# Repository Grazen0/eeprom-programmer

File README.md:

# EEPROM Programmer

Code to program an AT28C256 EEPROM using an Arduino MEGA. Consists of [firmware](firmware) for an Arduino Mega 2560, and an [uploader](uploader) that talks to the firmware via serial USB.

## Hardware

The firmware is designed to work with a custom-made board that can be inserted on top of the Arduino's side pin column.

|  |  |
| :-------------------------------------------------------: | :---------------------------------------------------------------------------: |

The schematic is as follows:

The pins labeled "Arduino MEGA" go on top the rightmost header columns of the Arduino.

## Usage

The uploader can be used as follows:

```bash
# You may specify a chain of "commands" to execute. More on commands below.

# Unlock, write a file, and lock again
eeprom-programmer \
    'unlock' \
    'write <file.bin>' \
    'lock'

# Read the EEPROM's first 256 bytes into out.bin
eeprom-programmer 'read out.bin --len=256'

# Doom
eeprom-programmer 'erase'
```

The CLI supports the following commands:

- `read <FILE> [--start=<ADDR>] [--len=<NUM>]`: Dumps the EEPROM's contents to `<FILE>`.
- `write <FILE> [--no-verify] [--verify-attempts=<NUM>]`: Writes `<FILE>` to the EEPROM starting at address 0.
- `verify <FILE> [--fix] [--max-attempts=<NUM>]`: Verifies the EEPROM against `<FILE>`.
- `unlock`: Executes the software data protection (SDP) disable algorithm.
- `lock`: Executes the SDP enable algorithm.
- `erase`: Executes the software chip erase algorithm.

## References

- [AT28C256 Datasheet](https://ww1.microchip.com/downloads/aemDocuments/documents/MPD/ProductDocuments/DataSheets/AT28C256-Industrial-Grade-256-Kbit-Paged-Parallel-EEPROM-Data-Sheet-DS20006386.pdf)
- [Software Chip Erase](http://ww1.microchip.com/downloads/en/Appnotes/doc0544.pdf)
- [Parallel EEPROM Data Protection](http://ww1.microchip.com/downloads/en/Appnotes/DOC0543.PDF)

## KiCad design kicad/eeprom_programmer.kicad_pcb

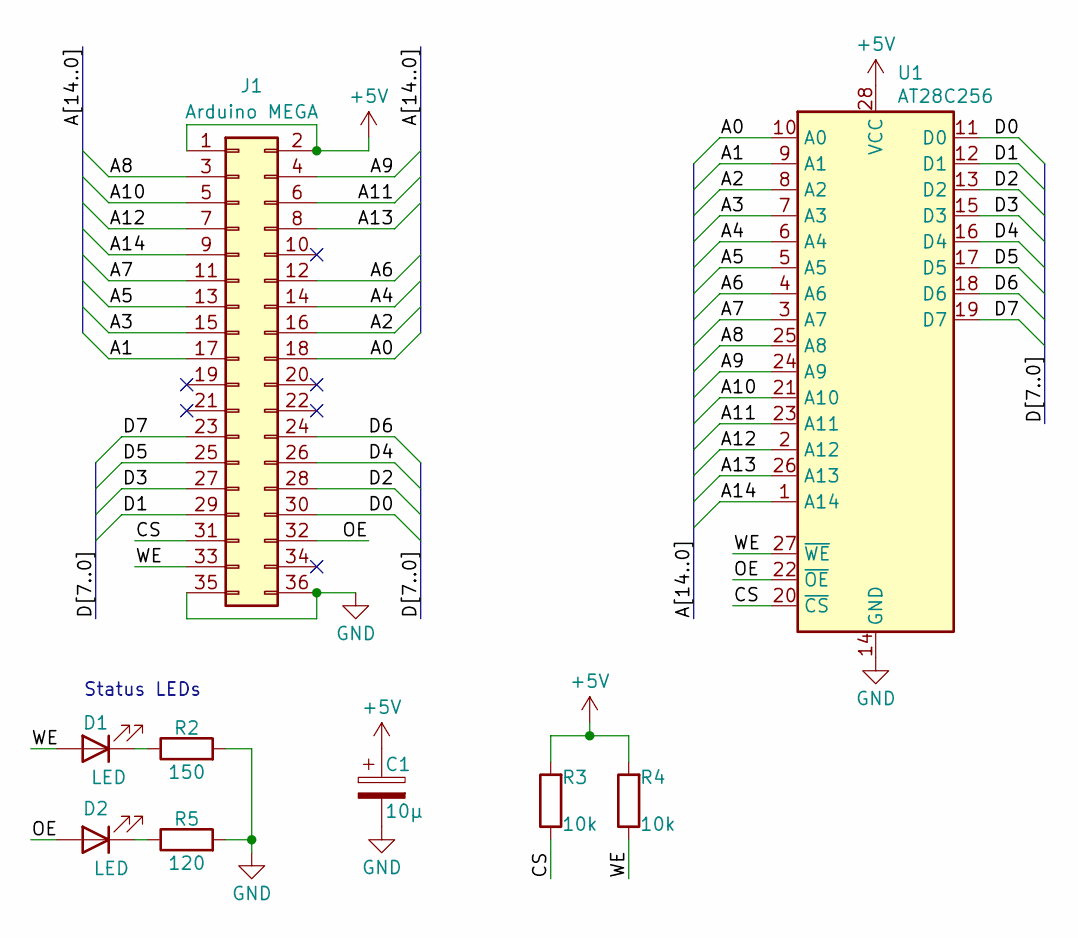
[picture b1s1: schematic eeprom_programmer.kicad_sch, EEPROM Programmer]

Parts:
C1: 10µ; CP_Radial_D5.0mm_P2.50mm
D1, D2: LED; LED_D5.0mm
J1: Arduino MEGA; PinHeader_2x18_P2.54mm_Vertical
R2: 150; R_Axial_DIN0207_L6.3mm_D2.5mm_P10.16mm_Horizontal
R3, R4: 10k; R_Axial_DIN0207_L6.3mm_D2.5mm_P10.16mm_Horizontal
R5: 120; R_Axial_DIN0207_L6.3mm_D2.5mm_P10.16mm_Horizontal
U1: AT28C256; DIP_Socket-28_W11.9mm_W12.7mm_W15.24mm_W17.78mm_W18.5mm_3M_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

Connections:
+5V: C1.1, J1.1, J1.2, R3.2, R4.2, U1.28 (VCC)
/A0: J1.18, U1.10 (A0)
/A1: J1.17, U1.9 (A1)
/A2: J1.16, U1.8 (A2)
/A3: J1.15, U1.7 (A3)
/A4: J1.14, U1.6 (A4)
/A5: J1.13, U1.5 (A5)
/A6: J1.12, U1.4 (A6)
/A7: J1.11, U1.3 (A7)
/A8: J1.3, U1.25 (A8)
/A9: J1.4, U1.24 (A9)
/A10: J1.5, U1.21 (A10)
/A11: J1.6, U1.23 (A11)
/A12: J1.7, U1.2 (A12)
/A13: J1.8, U1.26 (A13)
/A14: J1.9, U1.1 (A14)
/CS: J1.31, R3.1, U1.20 (~CS)
/D0: J1.30, U1.11 (D0)
/D1: J1.29, U1.12 (D1)
/D2: J1.28, U1.13 (D2)
/D3: J1.27, U1.15 (D3)
/D4: J1.26, U1.16 (D4)
/D5: J1.25, U1.17 (D5)
/D6: J1.24, U1.18 (D6)
/D7: J1.23, U1.19 (D7)
/OE: D2.2 (A), J1.32, U1.22 (~OE)
/WE: D1.2 (A), J1.33, R4.1, U1.27 (~WE)
GND: C1.2, J1.35, J1.36, R2.2, R5.2, U1.14 (GND)
unnamed: D1.1 (K), R2.1
unnamed: D2.1 (K), R5.1

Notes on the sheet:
Status LEDs

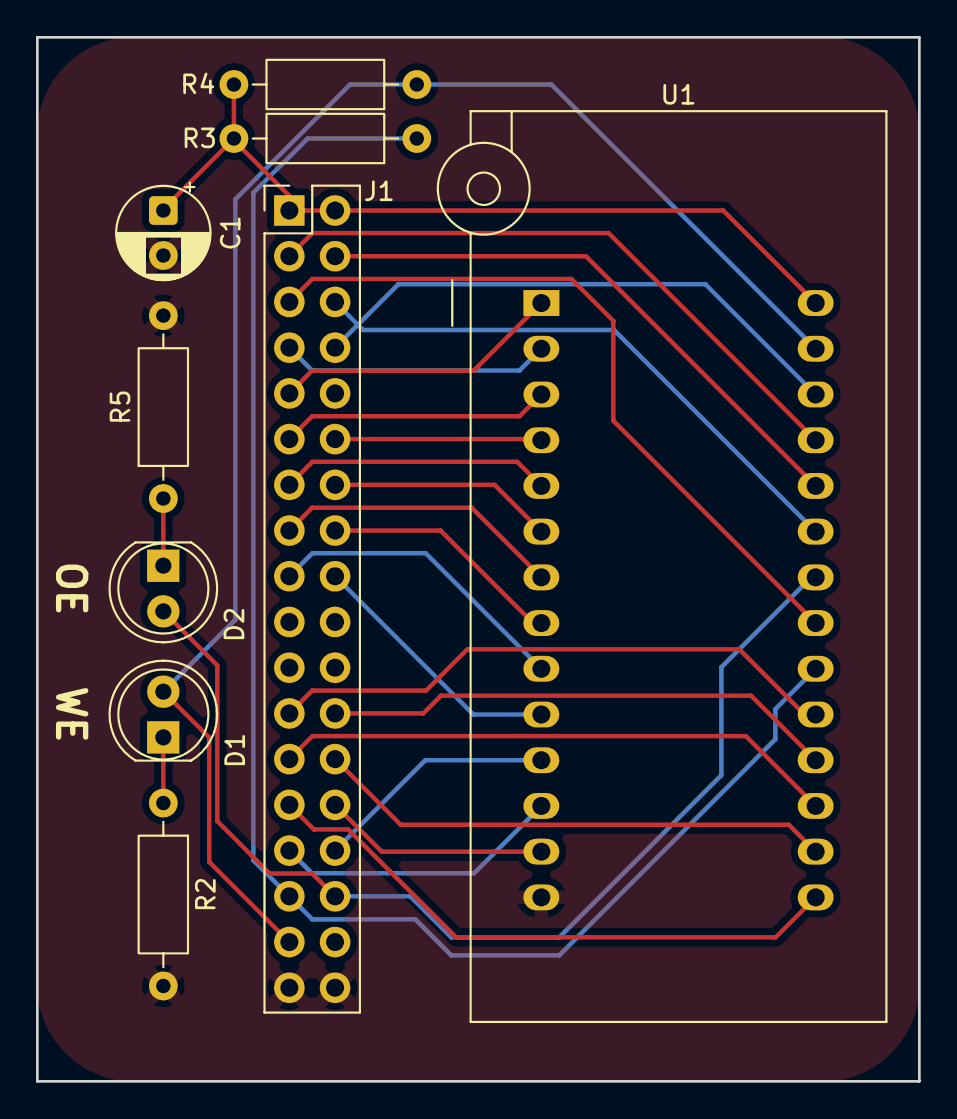
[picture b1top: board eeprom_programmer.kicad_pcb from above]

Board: 2 copper layers, 49.0 x 58.0 mm, 9 parts (0 on the bottom side), 30 nets.

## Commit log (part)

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2025-09-09 feat: init
2025-09-11 chore: add xxd to dev shell
2025-09-11 chore: add .local directories to .gitignore
2025-09-11 feat: finish read, write and verify commands
2025-09-12 chore(firmware): add .clang-format
2025-09-12 feat: add post-write verification and refactor code
2025-09-12 build: flake-ify project
2025-09-12 refactor(uploader): rename uploader package to simply "eeprom-programmer"
2025-09-12 fix(firmware): skip post-write fixing if not needed
2025-09-12 fix(uploader): write correct chunk size on chunk packet
2025-12-20 chore: add rust-analyzer to shell.nix
2025-12-20 feat: add software write enable/disable support
